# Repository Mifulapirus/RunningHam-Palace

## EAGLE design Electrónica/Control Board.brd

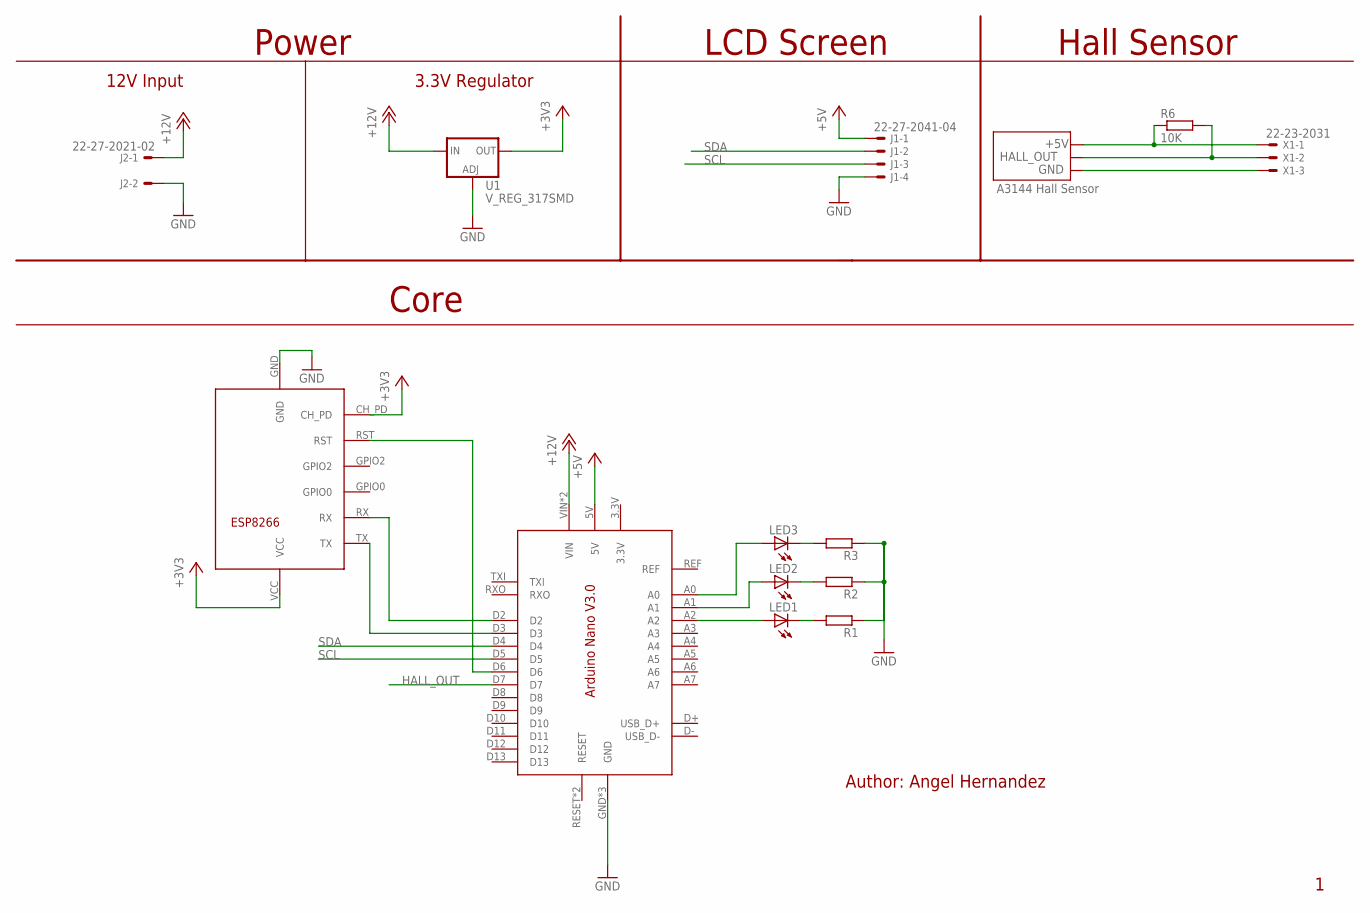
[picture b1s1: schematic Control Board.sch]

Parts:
J1: 22-27-2041-04; 6410-04
J2: 22-27-2021-02; 6410-02
LED1, LED2, LED3: LED5MM
R1, R2, R3: R-EU_0204/2V; 0204V
R6: 10K; 0204/7
U1: V_REG_317SMD; SOT223
U$1: ARDUINO_NANO_V3
U$2: ESP8266
X1: 22-23-2031

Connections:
+3V3: U1.2 (OUT), U$2.CH_PD, U$2.VCC
+5V: J1.1, R6.1, U$1.5V, X1.1
+12V: J2.1, U1.3 (IN), U$1.VIN, U$1.VUSB (VIN)
GND: J1.4, J2.2, R1.1, R2.1, R3.1, U1.1 (ADJ), U$1.GND, U$1.GND1 (GND), U$1.GND_USB (GND), U$2.GND, X1.3
HALL_OUT: R6.2, U$1.D7, X1.2
unnamed: LED1.A, U$1.A2
unnamed: U$1.D3, U$2.TX
unnamed: U$1.D2, U$2.RX
unnamed: LED2.A, U$1.A1
unnamed: LED3.A, U$1.A0
unnamed: LED1.K (C), R1.2
unnamed: LED2.K (C), R2.2
unnamed: LED3.K (C), R3.2
unnamed: U$1.D6, U$2.RST
SCL: J1.3, U$1.D5
SDA: J1.2, U$1.D4

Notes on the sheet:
Hall Sensor
Power
LCD Screen
Author: Angel Hernandez
12V Input
3.3V Regulator
Core
A3144 Hall Sensor

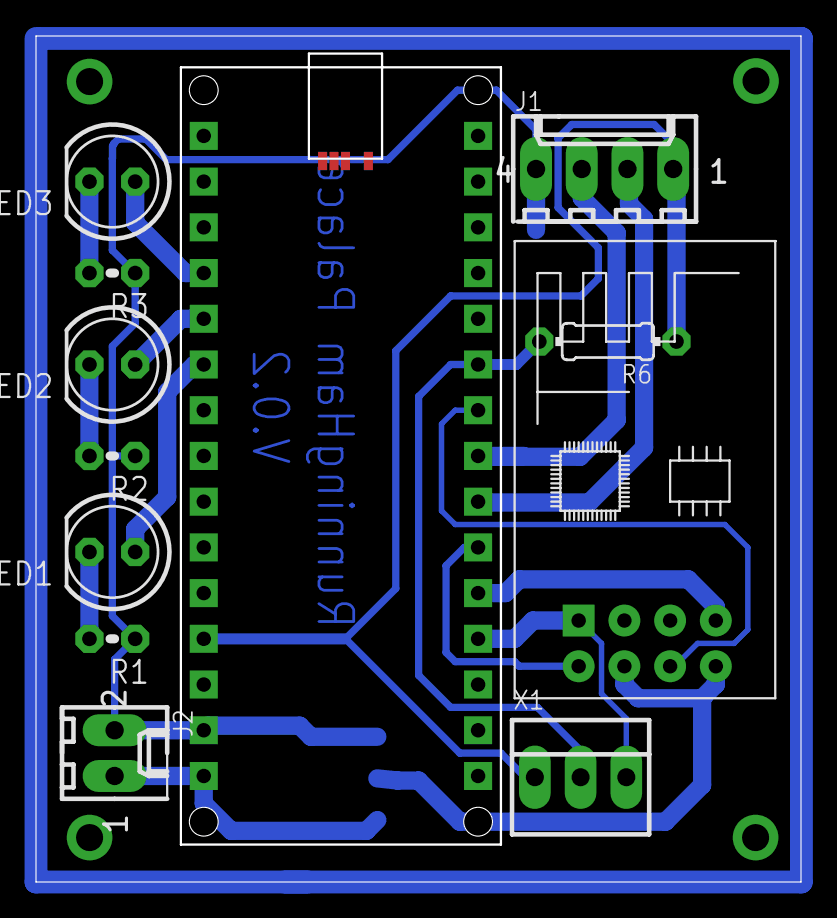
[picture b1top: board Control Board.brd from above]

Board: 2 copper layers, 42.4 x 46.9 mm, 13 parts (1 on the bottom side), 16 nets.

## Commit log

2015-04-18 Initial Commit - Firmware V0.1. It should work with interrupts and not by polling the sensor - Electronics: The Hall sensor should be moved to D2 or D3 for the next version
2015-04-18 Folder name changed
2015-04-18 Got rid of some worthless eeprom writing

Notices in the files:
parts and their libraries:
SparkFun-PowerIC: Licensing: Creative Commons ShareAlike 4.0 International - https://creativecommons.org/licenses/by-sa/4.0
